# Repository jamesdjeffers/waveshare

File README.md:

# Example and test code for Waveshare SimCom 7080 Modem

Implements an IoT device on the AT&T 4G newtwork using the Raspberry Pi module from Waveshare based on the SimCom 7080G modem device.
This project extends the capabilities of the company provided downloads and examples for international connection.
The programs use the Google Sheets API to upload interanl data to a shared database.

The Python examples run a complete configuration on the US based 4G network of AT&T
From the SimCom webstie the AT&T network is 4G LTE-M (CTE-M) with is "310410" on bands 2, 8, 12.
The device is configured using "AT" commands over serial port operating at 9600 baud.
For testing purposes a complete Windows based Python driver was devloped.
For field testing Arduino based C-code for an Adafruit Feather.

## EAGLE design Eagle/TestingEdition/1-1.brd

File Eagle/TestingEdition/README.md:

All testing edition here and testing library here!

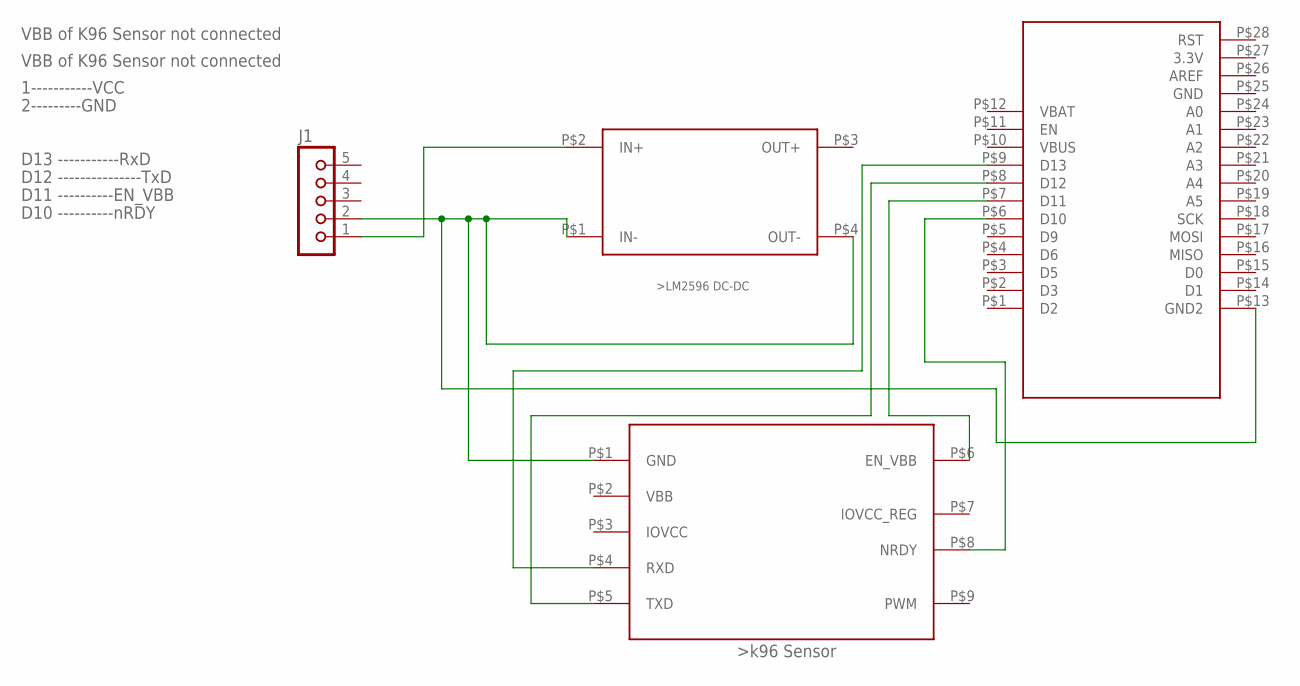
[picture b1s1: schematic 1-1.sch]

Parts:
DCDC1: DCDC
FEATHER1: FEATHER
J1: JU05
K96SENSOR1: K96SENSOR

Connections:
unnamed: DCDC1.P$2 (IN+), J1.1
unnamed: DCDC1.P$1 (IN-), DCDC1.P$4 (OUT-), FEATHER1.P$13 (GND2), J1.2, K96SENSOR1.P$1 (GND)
unnamed: FEATHER1.P$6 (D10), K96SENSOR1.P$8 (NRDY)
unnamed: FEATHER1.P$9 (D13), K96SENSOR1.P$4 (RXD)
unnamed: FEATHER1.P$8 (D12), K96SENSOR1.P$5 (TXD)
unnamed: FEATHER1.P$7 (D11), K96SENSOR1.P$6 (EN_VBB)

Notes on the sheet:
D13 -----------RxD
D12 ---------------TxD
D11 ----------EN_VBB
D10 ----------nRDY
VBB of K96 Sensor not connected
1-----------VCC
2---------GND

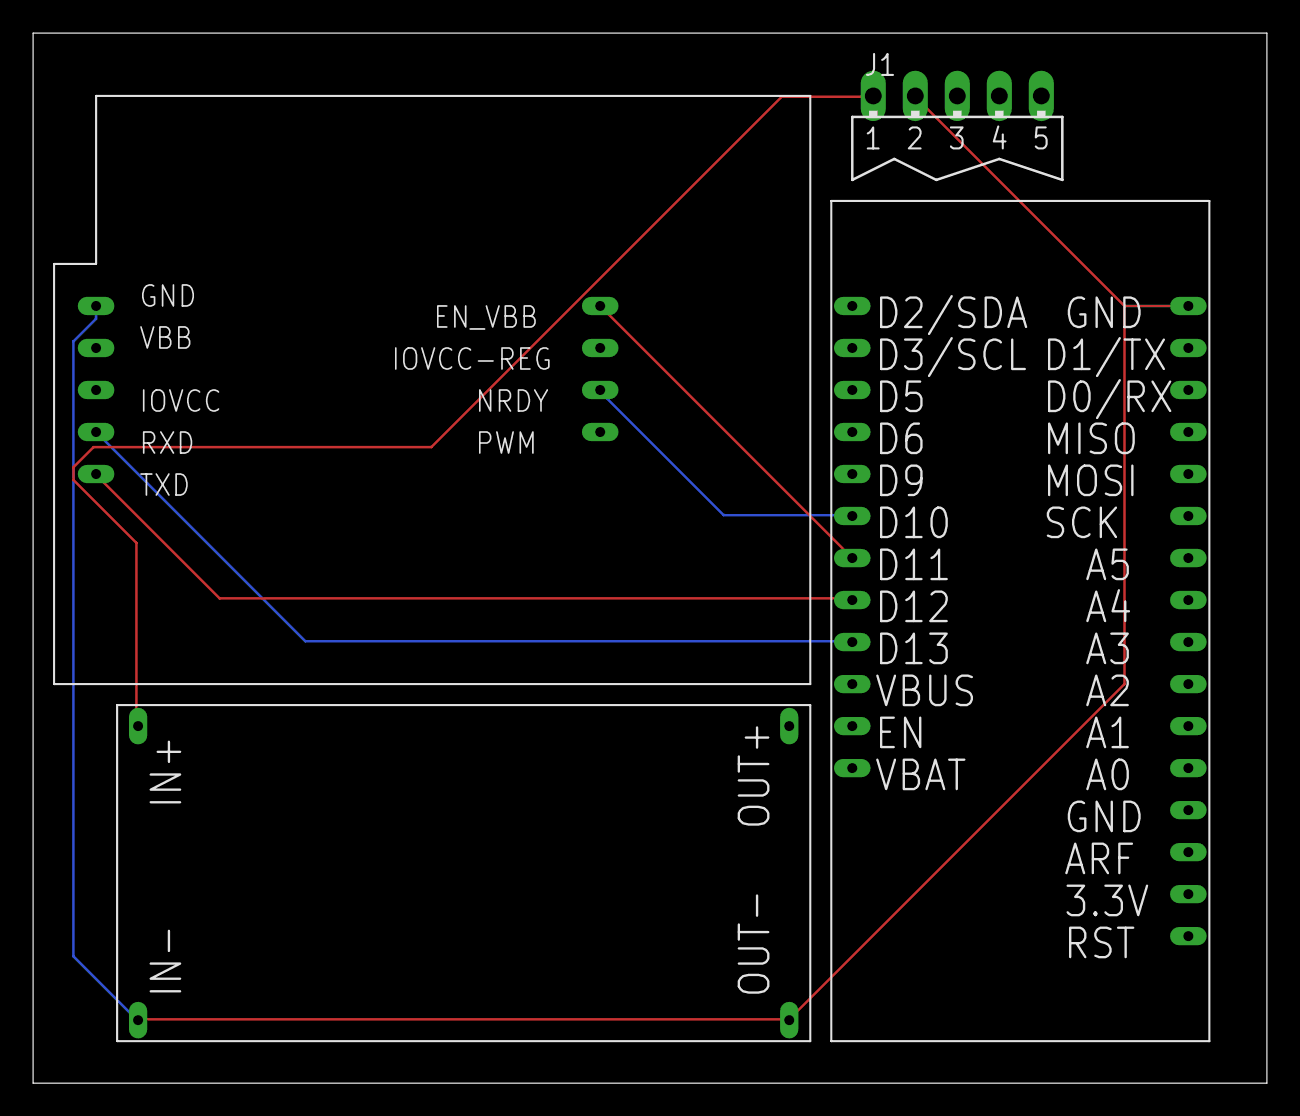
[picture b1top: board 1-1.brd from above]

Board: 2 copper layers, 74.6 x 63.5 mm, 4 parts (0 on the bottom side), 6 nets.

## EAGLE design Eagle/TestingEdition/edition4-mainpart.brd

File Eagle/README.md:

PCB design for Methane Senosr of University of Oklahoma

-----------------------------------------------------------------------------
Update 7/5                                                            
Edition 1 --- removed                                                                
Edition 2 --- 1x K96 Sensor, 1x Feather Mo, 1x Dc-Dc, 1x Power Supply                   
Edition 3 --- 1x K96 Sensor, 1x Feather Mo, 2x Dc-Dc, 1x Power Supply, 1x Resperry Pi                      
Edition 4 --- (1) Main part               
1x Feather Mo, 4x Dc-Dc, 3x Power Supply, 1x Resperry Pi, 1x8 Switch           
(2) Sensor part:    
1x K96 Sensor                   
Note: The diameter of drill hole of Edition 2 and Edition 3 is too small, Edition 4's drill hole's diameter is 1.5 times of original diameter      

----------------------------------------------------------------------------

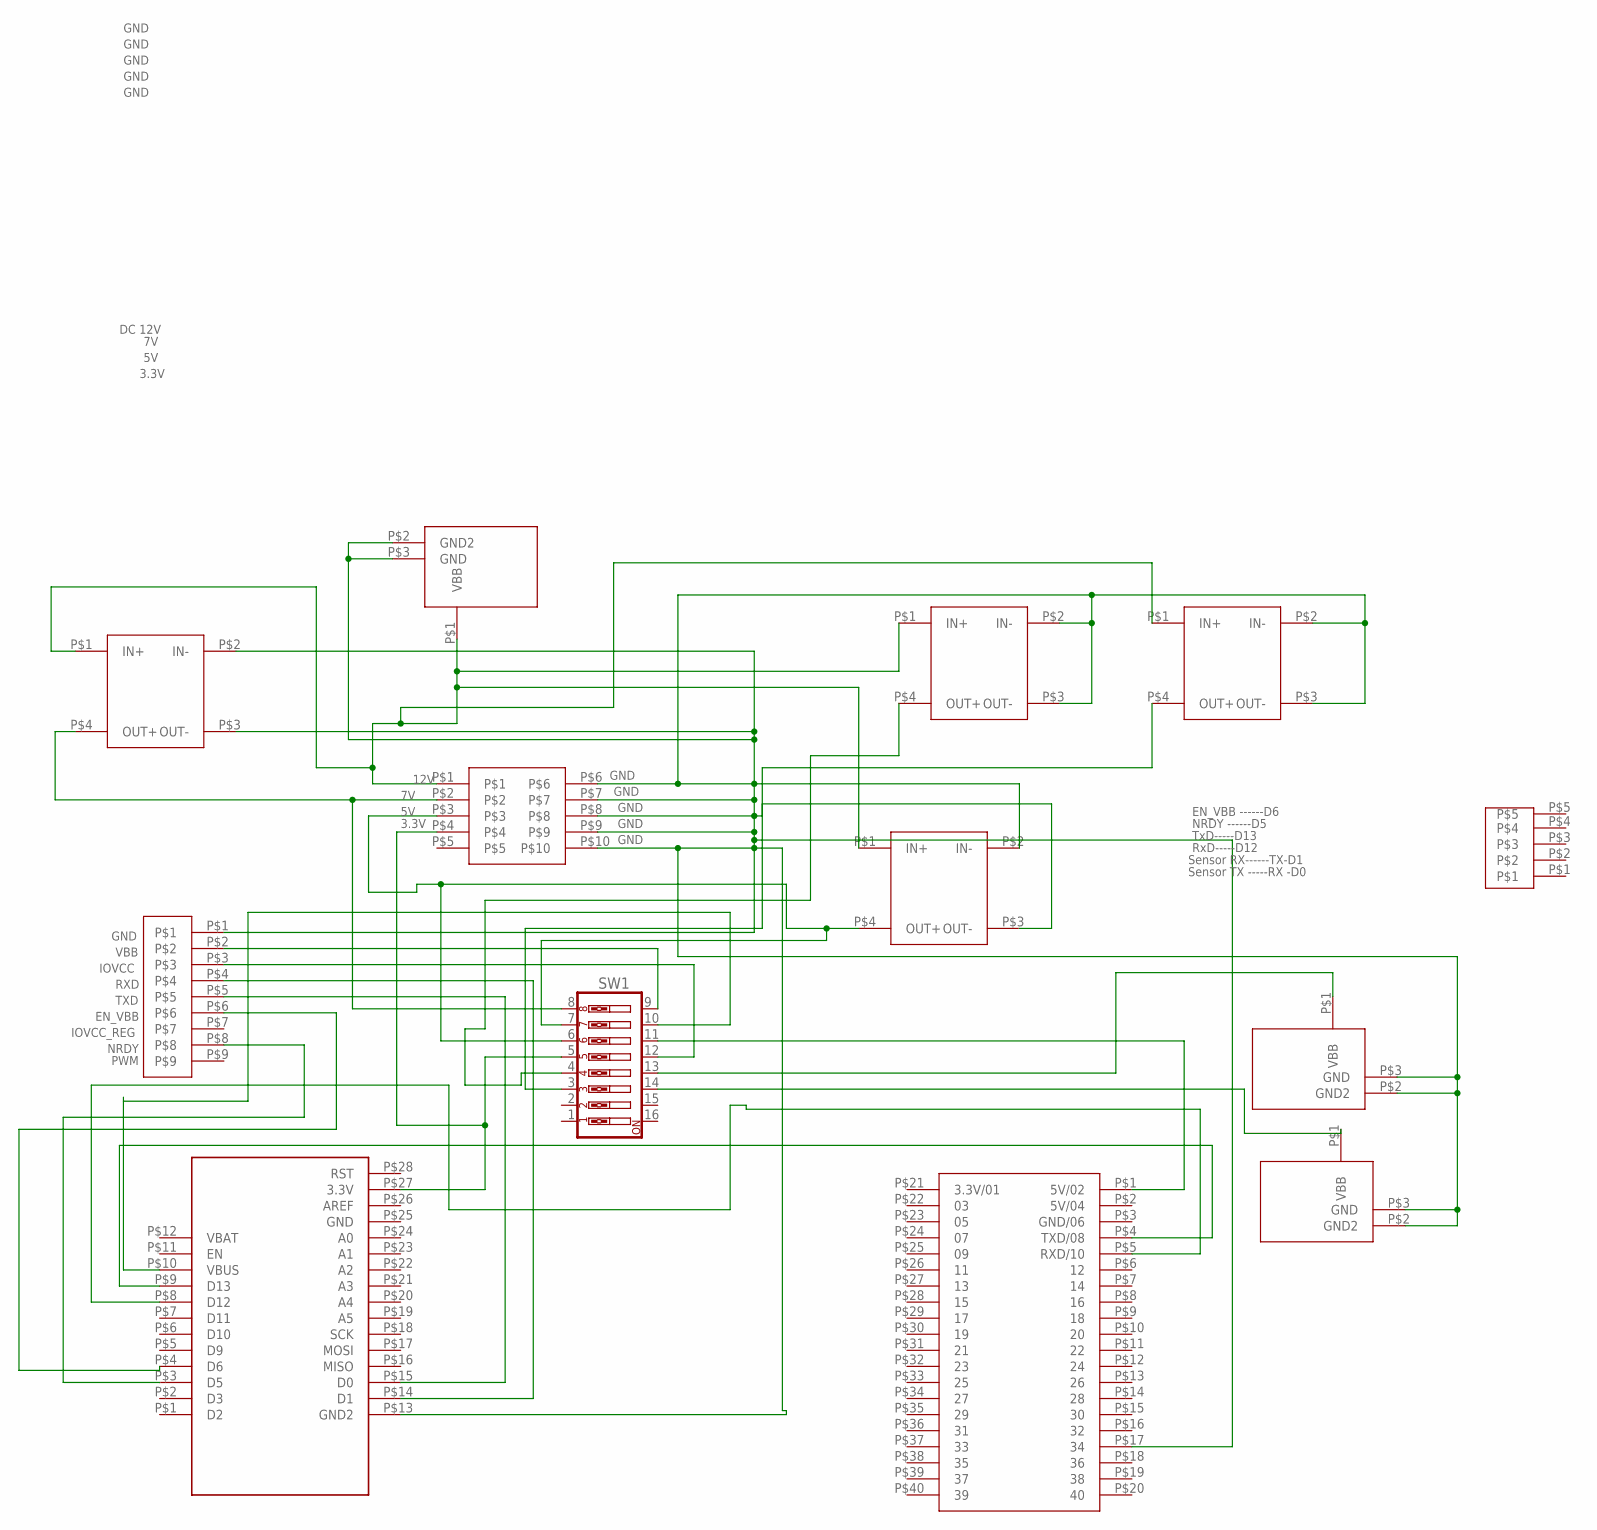
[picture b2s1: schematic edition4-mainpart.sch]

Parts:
SW1: SW_DIP-8; EDG-08
U$1, U$2, U$6, U$7: MH-MINI-360
U$3, U$4, U$5: POWER; POWERIN
U$8: PIN
U$10: FEATHER
U$11: RASPBERRYPI
U$14: 2X5FEET
U$15: 9FEETPIN

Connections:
unnamed: SW1.10, U$10.P$10 (VBUS)
unnamed: SW1.3, U$7.P$4 (OUT+)
unnamed: SW1.5, U$10.P$27 (3.3V), U$14.P$4
unnamed: SW1.8, U$6.P$4 (OUT+), U$14.P$2
unnamed: SW1.9, U$15.P$2
unnamed: U$10.P$3 (D5), U$15.P$8
unnamed: SW1.12, U$15.P$3
unnamed: U$10.P$14 (D1), U$15.P$4
unnamed: U$10.P$15 (D0), U$15.P$5
unnamed: U$10.P$4 (D6), U$15.P$6
unnamed: SW1.6, SW1.7, U$2.P$4 (OUT+), U$14.P$3
unnamed: SW1.11, U$11.P$1 (5V/02)
unnamed: SW1.13, U$5.P$1 (VBB)
unnamed: U$10.P$9 (D13), U$11.P$4 (TXD/08)
unnamed: U$10.P$8 (D12), U$11.P$5 (RXD/10)
unnamed: SW1.4, U$1.P$4 (OUT+)
unnamed: U$1.P$1 (IN+), U$2.P$1 (IN+), U$3.P$1 (VBB), U$6.P$1 (IN+), U$7.P$1 (IN+), U$14.P$1
unnamed: SW1.14, U$4.P$1 (VBB)
unnamed: U$1.P$2 (IN-), U$1.P$3 (OUT-), U$2.P$2 (IN-), U$2.P$3 (OUT-), U$3.P$2 (GND2), U$3.P$3 (GND), U$4.P$2 (GND2), U$4.P$3 (GND), U$5.P$2 (GND2), U$5.P$3 (GND), U$6.P$2 (IN-), U$6.P$3 (OUT-), U$7.P$2 (IN-), U$7.P$3 (OUT-), U$10.P$13 (GND2), U$11.P$17 (34), U$14.P$6, U$14.P$7, U$14.P$8, U$14.P$9, U$14.P$10, U$15.P$1

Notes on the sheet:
GND
DC 12V
3.3V
Sensor RX------TX-D1
TxD-----D13
RxD-----D12
EN_VBB ------D6
NRDY ------D5
Sensor TX -----RX -D0
PWM
NRDY
IOVCC_REG
EN_VBB
TXD
RXD
IOVCC
VBB
12V

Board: 2 copper layers, 13 parts (1 on the bottom side), 19 nets, no tracks yet.

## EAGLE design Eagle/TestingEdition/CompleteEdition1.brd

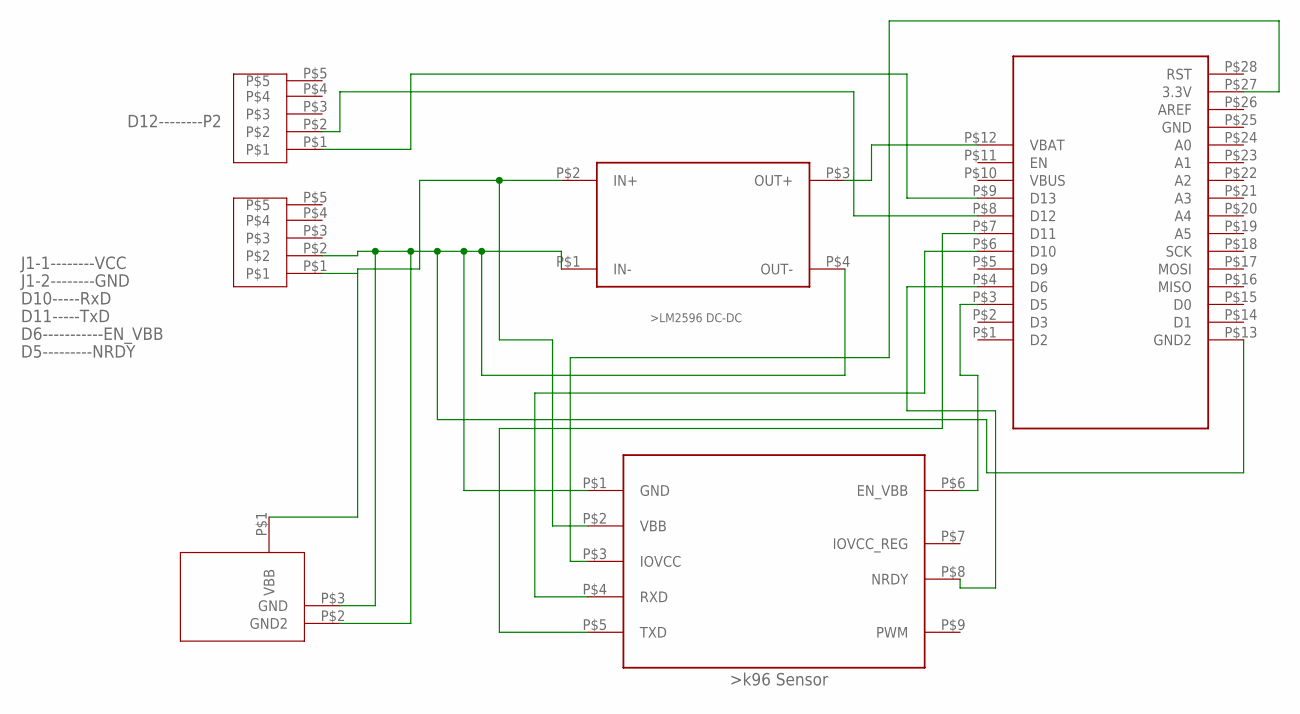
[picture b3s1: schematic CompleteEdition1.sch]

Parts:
DCDC1: DCDC
FEATHER1: FEATHER
K96SENSOR1: K96SENSOR
PIN1, PIN2: PIN
U$1: POWER; POWERIN

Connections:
unnamed: DCDC1.P$2 (IN+), K96SENSOR1.P$2 (VBB), PIN1.P$1, U$1.P$1 (VBB)
unnamed: DCDC1.P$1 (IN-), DCDC1.P$4 (OUT-), FEATHER1.P$13 (GND2), K96SENSOR1.P$1 (GND), PIN1.P$2, U$1.P$2 (GND2), U$1.P$3 (GND)
unnamed: FEATHER1.P$6 (D10), K96SENSOR1.P$4 (RXD)
unnamed: DCDC1.P$3 (OUT+), FEATHER1.P$12 (VBAT)
unnamed: FEATHER1.P$7 (D11), K96SENSOR1.P$5 (TXD)
unnamed: FEATHER1.P$4 (D6), K96SENSOR1.P$8 (NRDY)
unnamed: FEATHER1.P$9 (D13), PIN2.P$1
unnamed: FEATHER1.P$3 (D5), K96SENSOR1.P$6 (EN_VBB)
unnamed: FEATHER1.P$27 (3.3V), K96SENSOR1.P$3 (IOVCC)
unnamed: FEATHER1.P$8 (D12), PIN2.P$2

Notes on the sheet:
D10-----RxD
D11-----TxD
D6-----------EN_VBB
D5---------NRDY
J1-1--------VCC
J1-2--------GND
D12--------P2

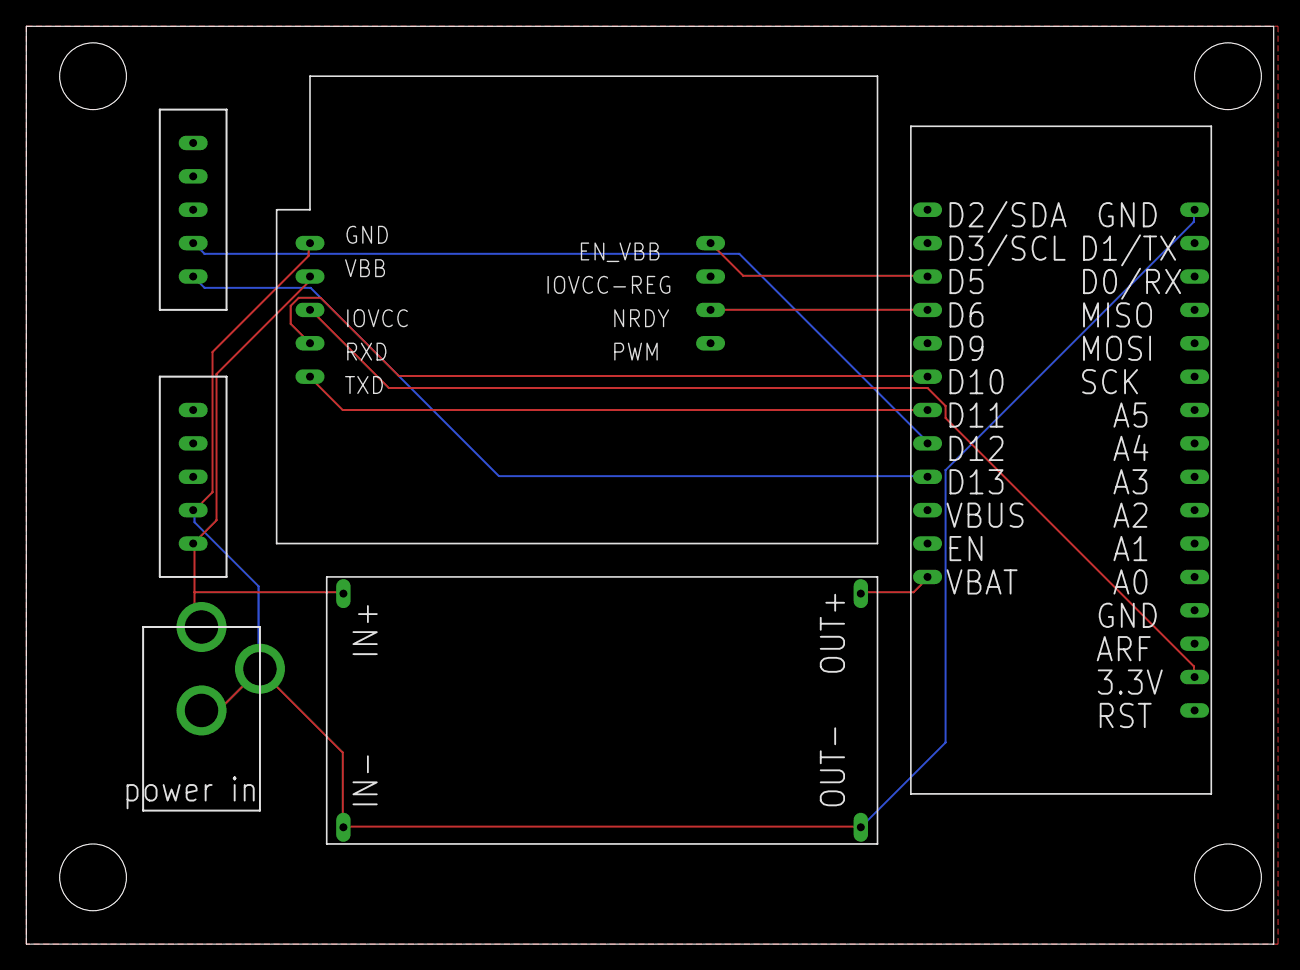
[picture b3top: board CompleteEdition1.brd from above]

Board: 2 copper layers, 94.9 x 69.8 mm, 6 parts (0 on the bottom side), 10 nets.

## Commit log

2022-07-01 First upload
    Known issues with modem initialization
    Known issues with NTP clock.
2022-07-01 testing fork
    first attempt
2022-07-05 EagleEdition4Uploaded
    EagleEdition4
2022-07-05 Create Eagle
2022-07-05 Uploaded Eagle File
2022-07-20 Hardware version 3 with working FTP modem code
    Works with modem power pin on Feather D5 and the serial GPS disabled.
    All FTP login information is removed from statements.
    Replace all case-specific "TODO" with account and password info prior to device upload.
2022-07-25 Removed internal clock operations file.
2022-07-25 Added internal log file with tracking
    Updated to fully operational FTP with recovery options for power loss.
    Serial print statements replaced with time-stamp text line written to SD card.
2022-07-25 Removed login information
2022-07-28 Formal data for Python examples
2022-10-03 Python scripts for direct modem connection.
    Initial test code working on Windows PC edited from Waveshare examples for the Raspberry Pi.
2022-11-10 New FTP upload algorithm
    Updates for better usability
    Changed the timing and retries for FTP uploads and downloads.
2023-02-15 Updates for non-blocking modem operation
    Modified code from Capstone branch.
2023-03-21 Functions for FTP debug
2023-06-12 Fast response without modem
    General changes for future development. Removed wait time operations
2023-06-14 Serial data for 3 thermocouples
    Implements 3 MAX thermocouples from Adafruit.
2023-08-18 Update README.md
    Fixed modem number and typo in text
2023-09-05 Added anonymous FTP features
    Added some delays and error checking to FTP server operations
    Deleted all password and login information
    Added comments
2023-09-08 Improved FTP operation
    Added wait loop to check for data NOT ready message from FTP server.
    Improved comments.
2023-10-18 New class for using SSH and SFTP
    Automates server access and FTP file copy. Also appends small data files into one larger file.
2023-10-18 Rename and Delete unused files
    Reorganize code files
2023-10-18 Update to v0.9
    Added extra time delays for modem restart. Improved FTP code for delays (still does not retry interrupted transfer)
2023-11-09 Fix merge mistakes
    Working code recovered from bad merge. Operates devices with GPS and blinks.
2023-11-09 New file for Sniffer4D
    Cut and paste previous serial code to receive strings and append. Runs on Raspberry Pi.
2023-11-10 Continuation of merge failure
    Copied certain functions in K96 and Modem from previous merge.
2023-11-14 Added MQTT functions
    Added MQTT start and MQTT status commands.
    Changed all PDP configuration to index 0.
2023-11-17 Added support for new modem
    Fixed problem with modem initialization that caused infinite loop. Added pre-compiler directive support for second modem type. New power loop (no sleep mode pin implemented). Improved MQTT support fo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
2023-11-27 Created virtual SD
    Added virtual SD card for data and log storage when physical media fails.
    Creates a 1 kB string for log. Appends strings.
    Creates a 2 kB string for data. Appends strings.
    Does not trigger based on size, time intervals cause upload.
    Added HTML read options to modem.
2023-11-28 Fixed small memory leak in virtual SD card
    Cleaned up small bugs in virtual SD card code.
2023-11-28 Fixed multiple small bugs, added MQTT subscribe
    Small bugs for serial printing, logging, and others fixed.
    Multiple comments added.
    Added multiple MQTT functions.
    Successful MQTT subscribe without SSL.
2023-11-29 Implement MQTT subscribe
    Increased version number for MQTT options.
    Working subscribe, publish, and parse for basic MQTT to port 1883.
    Configures all settings except SSL (using https://test.mosquitto.org/)
    Changed configuration download option to include FTP and MQTT.
2023-11-30 Tested MQTT subscribe for configuration
    Tested reliable connection to reading MQTT port 1883.
    New read function to combine configuration, connection, subscribe, and unsubscribe.
    Tracks error and works simultaneously with FTP operations.
2023-12-01 Added high-level functions for MQTT and SSL
    Added high-level function calls to combine steps for SSL and MQTT connections. Tested MQTT with SSL. Fails with macro definition removing carriage returns. Worked with SD card version.
2023-12-19 Disabled upload for bench test
    Failed to read settings from SD card.
2024-01-05 Updates for version 3 Hardware
    Fixed modem reset problem from not initializing the digital output to "off" state. Fixed bug in FTP code by reading new FTP filename before upload. Made the SSH server code a GUI.
2024-01-05 Added regular MQTT data upload
2024-01-17 Updates to 0.10.3
    Updates for field testing. Includes unique MQTT topic. Changed clock reading functions.
2024-02-06 Improved modem startup
    Improved startup. Fixed logic for determining on/off state.
2024-02-15 Version 0.11.0
    Encrypted MQTT communications
